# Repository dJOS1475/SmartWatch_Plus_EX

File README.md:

# SmartWatch_Plus_EX
SmartWatch+ Tandy 1000 EX Edition

The Tandy 1000 EX SmartWatch+ module adds a Clock & Calendar to your 1000 EX. All you need to do is install it under the BIOS ROM and then use the Y2K Patched SMWCLOCK.COM utility to set the time automatically via your Autoexec.bat file.

I made this design because the original SmartWatch batteries are now mostly dead and can't be replaced. The 1000 SmartWatch+ uses a standard CR1632 Lithium coin cell for long life and easy replacement.

Y2K SmartWatch Software is here: https://www.dropbox.com/s/kctqpwzjxgymfz9/smwy2k.zip?dl=0

My Store can be found here: https://www.tindie.com/stores/CyberneticSys/

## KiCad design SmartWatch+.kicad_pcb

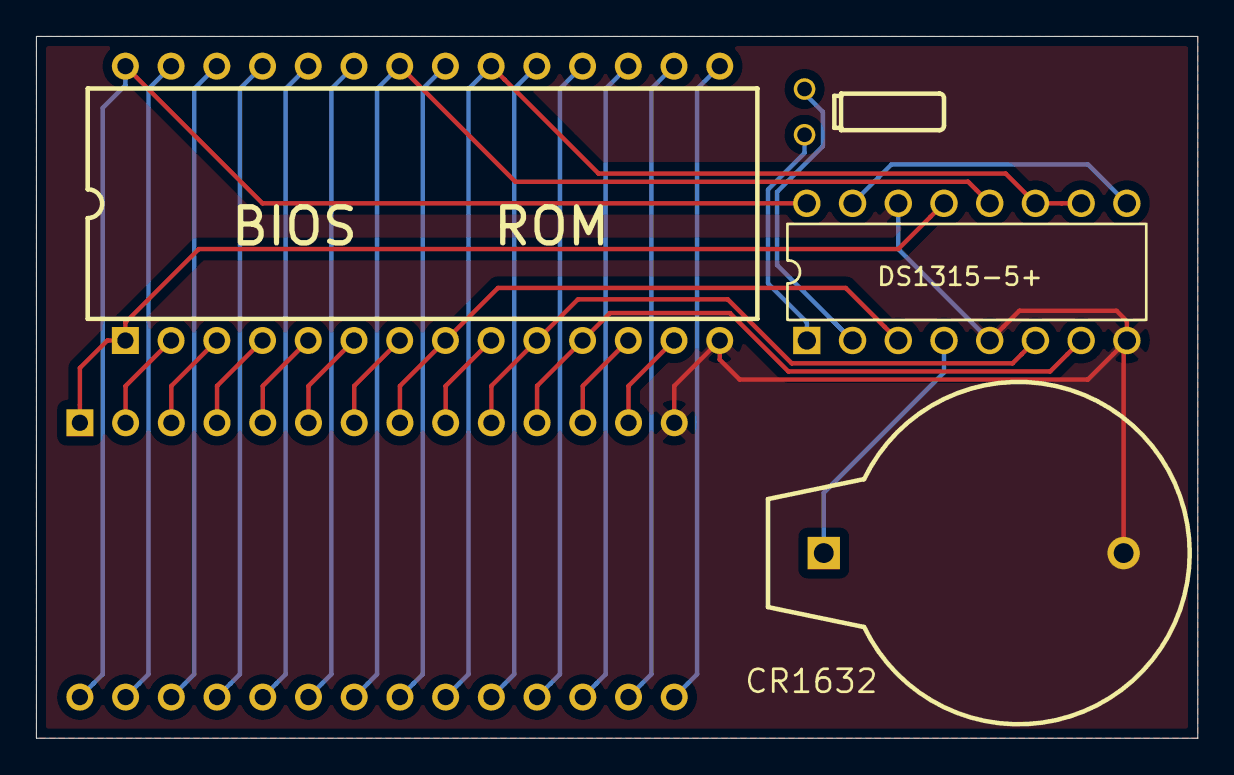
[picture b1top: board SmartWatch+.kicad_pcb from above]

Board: 2 copper layers, 64.5 x 39.0 mm, 5 parts (1 on the bottom side), 32 nets.

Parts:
3.768kHz1: Crystal Oscillator; TC26H
BT1: CR1632; BH600
IC1: DS1315-5+; DS1315-5&plus_
J1, J2: 2-1571586-9; DIP-28_600mil_SW

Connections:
/A1: IC1.13, J1.1, J2.1
/A2: J1.2, J2.2
/A3: J1.3, J2.3
/A4: J1.4, J2.4
/A5: J1.5, J2.5
/A6: J1.6, J2.6
/A7: J1.7, J2.7
/A8: IC1.3, J1.8, J2.8
/A9: J1.9, J2.9
/A10: IC1.6, J1.10, J2.10
/A11: IC1.7, J1.11, J2.11
/A12: J1.12, J2.12
/A13: J1.13, J2.13
/A15: J1.15, J2.15
/A16: J1.16, J2.16
/A17: J1.17, J2.17
/A18: J1.18, J2.18
/A19: J1.19, J2.19
/A20: IC1.10, IC1.11, J1.20, J2.20
/A21: J1.21, J2.21
/A22: IC1.12, J1.22, J2.22
/A23: J1.23, J2.23
/A24: J1.24, J2.24
/A25: J1.25, J2.25
/A26: J1.26, J2.26
/A27: J1.27, J2.27
/A28: IC1.16, J1.28, J2.28
GND: BT1.2, IC1.5, IC1.8, IC1.14, J1.14, J2.14
unnamed: 3.768kHz1.1, IC1.2
unnamed: 3.768kHz1.2, IC1.1
unnamed: BT1.1, IC1.4
unnamed: IC1.9, IC1.15
